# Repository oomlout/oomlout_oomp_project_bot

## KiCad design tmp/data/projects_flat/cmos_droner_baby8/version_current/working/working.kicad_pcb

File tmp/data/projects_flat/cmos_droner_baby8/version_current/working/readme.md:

# baby8 by cmos-droner  
This is a harvested standardized copy of a project from github.  
The original project can be found at:  
https://github.com/cmos-droner/baby8  
Please consult that link for additional, details, files, and license information.  
Note: It was auto harvested and if the original repo had more than one board file or anything out of the ordinary the files here are likely not representative.

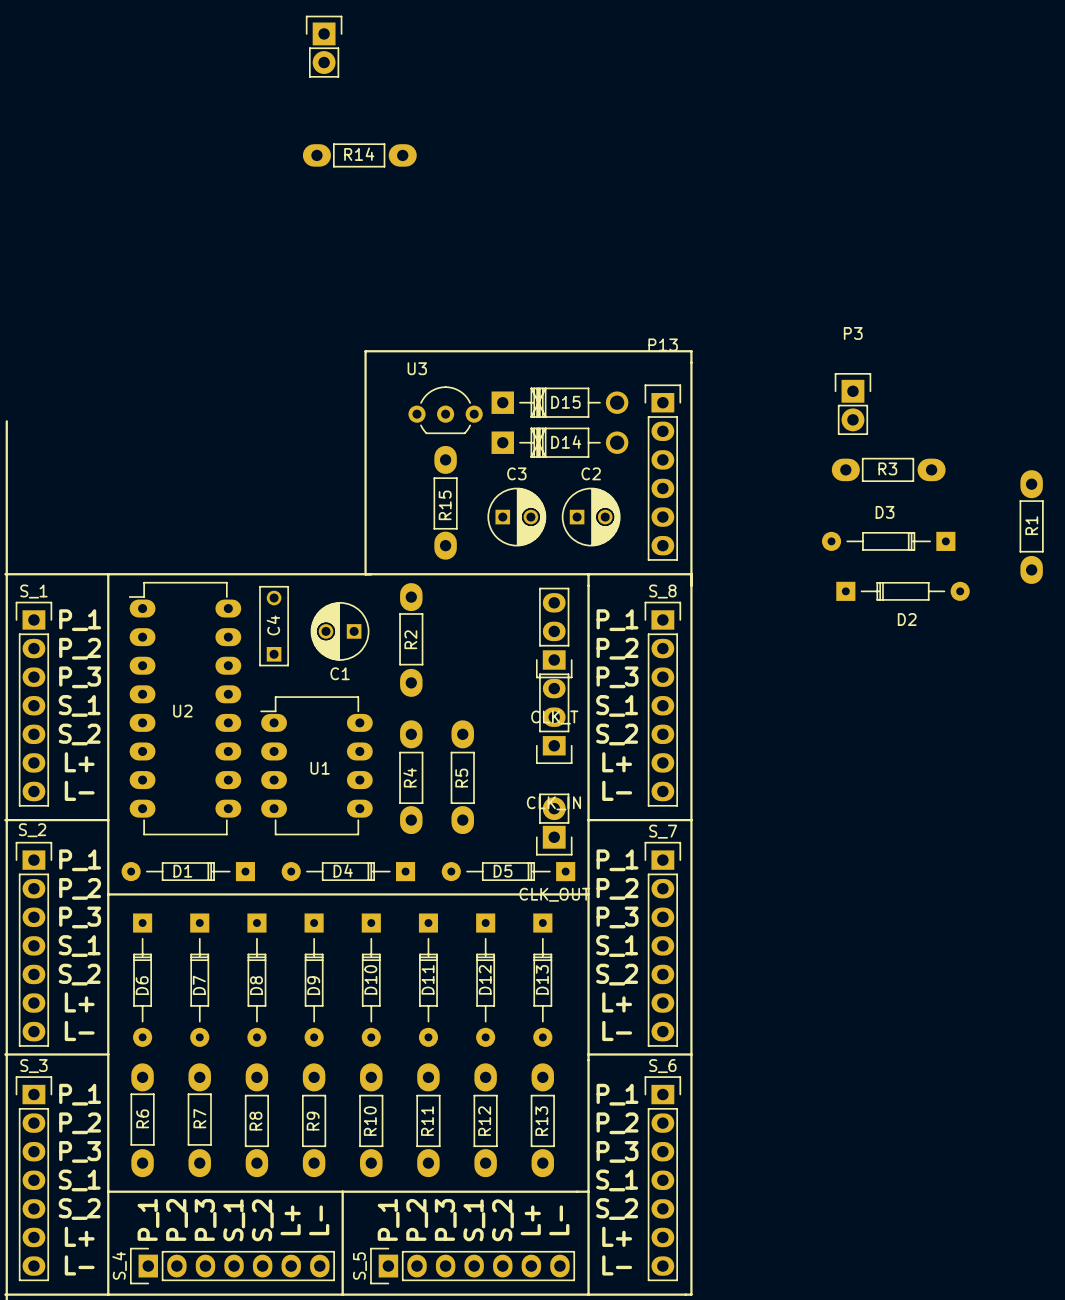
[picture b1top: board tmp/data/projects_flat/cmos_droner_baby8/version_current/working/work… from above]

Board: 2 copper layers, 51 parts (0 on the bottom side), 47 nets, no tracks yet.

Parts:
C1: 10uF; C_Radial_D5_L11_P2.5
C2: 220uF; C_Radial_D5_L11_P2.5
C3: 47uF; C_Radial_D5_L11_P2.5
C4: 100nF; C_Rect_L7_W2.5_P5
CLK_IN: CLK_IN; Pin_Header_Straight_1x03
CLK_OUT: CLK_OUT; Pin_Header_Straight_1x02
CLK_T: CLK_TIME; Pin_Header_Straight_1x03
D1, D2, D3, D4, D5, D6, D7, D8, D9, D10, D11, D12, D13: 1N4148; Diode_DO-35_SOD27_Horizontal_RM10
D14, D15: 1N4004; Diode_DO-41_SOD81_Horizontal_RM10
P3: RST; Pin_Header_Straight_1x02
P13: PWR; Pin_Header_Straight_1x06
P14: CV_OUT; Pin_Header_Straight_1x02
R1, R2, R5, R14: 1k; Resistor_Horizontal_RM7mm_Wide
R3, R4: 20k; Resistor_Horizontal_RM7mm_Wide
R6, R7, R8, R9, R10, R11, R12, R13, R15: 10k; Resistor_Horizontal_RM7mm_Wide
S_1: STEP_1; Pin_Header_Straight_1x07
S_2: STEP_2; Pin_Header_Straight_1x07
S_3: STEP_3; Pin_Header_Straight_1x07
S_4: STEP_4; Pin_Header_Straight_1x07
S_5: STEP_5; Pin_Header_Straight_1x07
S_6: STEP_6; Pin_Header_Straight_1x07
S_7: STEP_7; Pin_Header_Straight_1x07
S_8: STEP_8; Pin_Header_Straight_1x07
U1: LM555N; DIP-8_W7.62mm_LongPads
U2: 4017; DIP-16_W7.62mm_LongPads
U3: LM7805; TO-92_Inline_Wide

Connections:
+5V: C3.1, C4.1, CLK_T.1, D2.1, D4.1, D15.2, U1.4, U1.8, U2.16, U3.3
GND: C1.2, C2.2, C3.2, C4.2, CLK_IN.1, CLK_OUT.1, D3.2, D5.2, D14.2, P3.1, P13.1, P13.6, P14.1, R1.2, R5.1, S_1.3, S_1.7, S_2.3, S_2.7, S_3.3, S_3.7, S_4.3, S_4.7, S_5.3, S_5.7, S_6.3, S_6.7, S_7.3, S_7.7, S_8.3, S_8.7, U1.1, U2.8, U3.2
unnamed: C1.1, R2.2, U1.2, U1.6
unnamed: C2.1, D14.1, D15.1, P13.4, R15.2, U3.1
unnamed: CLK_OUT.2, D1.1
unnamed: D1.2, R4.2, U2.14
unnamed: D2.2, D3.1, P3.2, R1.1, R3.2
unnamed: CLK_IN.3, D4.2, D5.1, R4.1, R5.2
unnamed: D6.1, S_1.4
unnamed: D6.2, S_1.2
unnamed: D7.1, S_2.4
unnamed: D7.2, S_2.2
unnamed: D8.1, S_3.4
unnamed: D8.2, S_3.2
unnamed: D9.1, S_4.4
unnamed: D9.2, S_4.2
unnamed: D10.1, S_5.4
unnamed: D10.2, S_5.2
unnamed: D11.1, S_6.4
unnamed: D11.2, S_6.2
unnamed: D12.1, S_7.4
unnamed: D12.2, S_7.2
unnamed: D13.1, S_8.4
unnamed: D13.2, S_8.2
unnamed: CLK_IN.2, U1.3
unnamed: CLK_T.2, CLK_T.3, R2.1, U1.7
unnamed: R6.2, S_1.1, U2.3
unnamed: R6.1, S_1.6
unnamed: R7.2, S_2.1, U2.2
unnamed: R7.1, S_2.6
unnamed: R8.2, S_3.1, U2.4
unnamed: R8.1, S_3.6
unnamed: R9.2, S_4.1, U2.7
unnamed: R9.1, S_4.6
unnamed: R10.2, S_5.1, U2.10
unnamed: R10.1, S_5.6
unnamed: R11.2, S_6.1, U2.1
unnamed: R14.2, S_1.5, S_2.5, S_3.5, S_4.5, S_5.5, S_6.5, S_7.5, S_8.5
unnamed: R11.1, S_6.6
unnamed: R12.2, S_7.1, U2.5
unnamed: R12.1, S_7.6
unnamed: R13.2, S_8.1, U2.6
unnamed: R13.1, S_8.6
unnamed: P13.2, P13.3
unnamed: P13.5, R15.1
unnamed: P14.2, R14.1
unnamed: R3.1, U2.9, U2.15

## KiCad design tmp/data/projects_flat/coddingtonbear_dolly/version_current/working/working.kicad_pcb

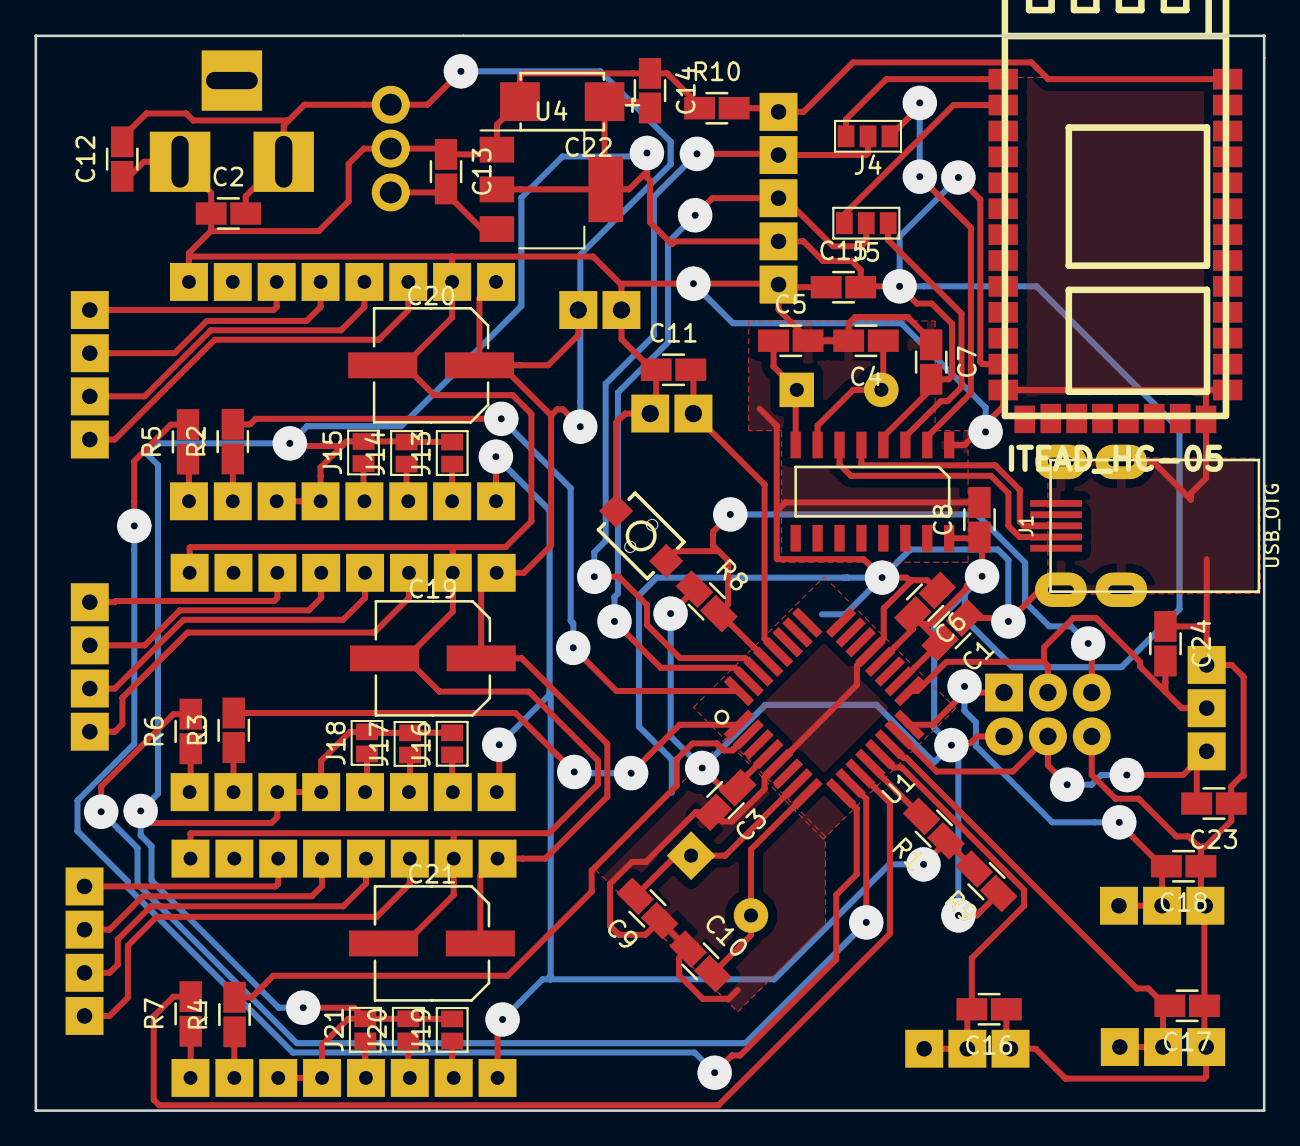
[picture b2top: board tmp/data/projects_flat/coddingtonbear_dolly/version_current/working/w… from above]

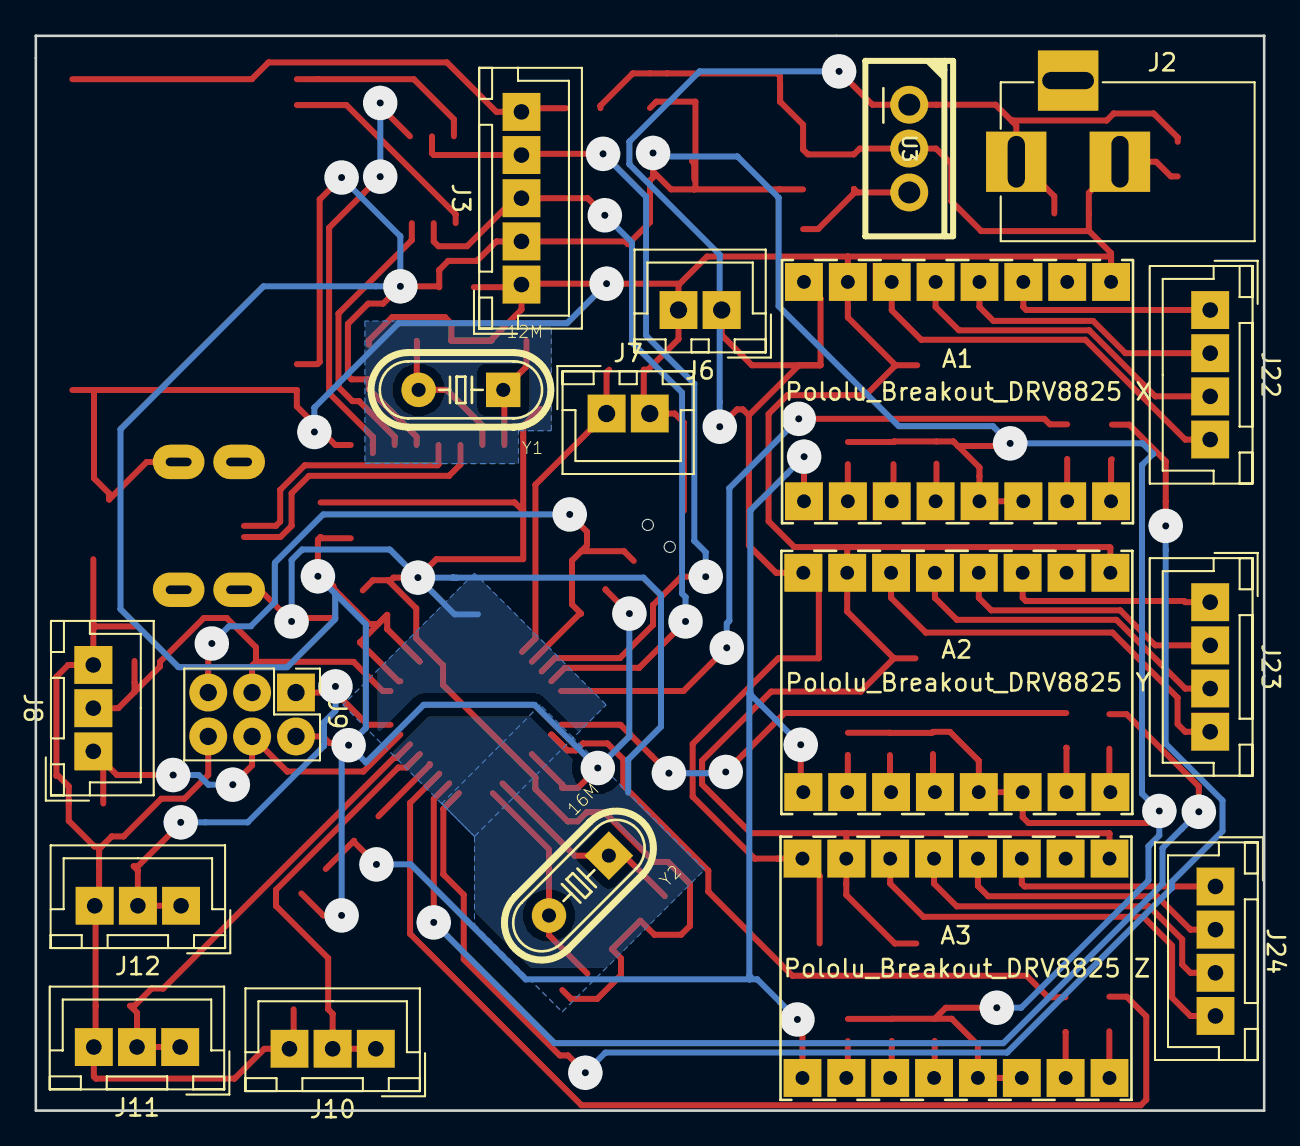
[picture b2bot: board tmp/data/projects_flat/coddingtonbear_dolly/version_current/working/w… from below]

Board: 2 copper layers, 71.1 x 62.2 mm, 69 parts (18 on the bottom side), 59 nets.

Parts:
A1: Pololu_Breakout_DRV8825 X; Pololu_Stepper_Breakout
A2: Pololu_Breakout_DRV8825 Y; Pololu_Stepper_Breakout
A3: Pololu_Breakout_DRV8825 Z; Pololu_Stepper_Breakout
C1, C2, C3, C6, C7, C8, C11, C14, C15, C16, C17, C18, C23, C24: 0.1u; 0805_Milling
C4, C5, C9, C10: 22p; 0805_Milling
C12, C13: 0.33u; 0805_Milling
C19, C20, C21: 100u; CAP-SMD-SIZE-D
C22: 220u; CAPACITOR_TANTALUM_C
J1: USB_OTG; UJ2-MIBH-4-SMT
J2: Barrel_Jack; BARREL_JACK
J3: UART; JST_XH_B05B-XH-A_05x2.50mm_Straight_LargePads
J4: RX; GS3
J5: TX; GS3
J6: 24V_Out; JST_XH_B02B-XH-A_02x2.50mm_Straight_LargePads
J7: Probe; JST_XH_B02B-XH-A_02x2.50mm_Straight_LargePads
J8: Spindle; JST_XH_B03B-XH-A_03x2.50mm_Straight_LargePads
J9: ICSP; Pin_Header_Straight_2x03_Pitch2.54mm
J10: X_End; JST_XH_B03B-XH-A_03x2.50mm_Straight_LargePads
J11: Y_End; JST_XH_B03B-XH-A_03x2.50mm_Straight_LargePads
J12: Z_End; JST_XH_B03B-XH-A_03x2.50mm_Straight_LargePads
J13, J14, J15, J16, J17, J18, J19, J20, J21: GS2
J22: X_Stepper; JST_XH_B04B-XH-A_04x2.50mm_Straight_LargePads
J23: Y_Stepper; JST_XH_B04B-XH-A_04x2.50mm_Straight_LargePads
J24: Z_Stepper; JST_XH_B04B-XH-A_04x2.50mm_Straight_LargePads
R1, R2, R3, R4, R5, R6, R7: 100; 0805_Milling
R8, R9, R10: 10k; 0805_Milling
SW1: SW_SPST; SW_PUSHBUTTON_TINY_2PIN
U1: ATMEGA328PB-AU; TQFP32_ATMEGA328P
U2: CH340G; SOIC-16
U3: L7805; TO-220
U4: AP1117-15; SOT-223-3Lead_TabPin2
U5: ITEAD_HC-05
Y1: 12M; XTAL_HC-49US-16.000MHZ
Y2: 16M; XTAL_HC-49US-16.000MHZ

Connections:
+3V3: A1.13, A1.14, A2.13, A2.14, A3.13, A3.14, C1.2, C3.1, C6.2, C7.2, C8.1, C14.2, C15.2, C22.1, J3.2, J9.2, J13.2, J14.2, J15.2, J16.2, J17.2, J18.2, J19.2, J20.2, J21.2, R8.1, R9.1, U1.4, U1.18, U1.20, U2.4, U2.16, U4.2, U5.12
+24V: A1.8, A2.8, A3.8, C2.2, C12.2, C19.1, C20.1, C21.1, J2.1, J6.1, U3.1
BT_IN: J5.1, U5.2
BT_KEY: J3.5, R10.2, U5.34
BT_OUT: J4.1, U5.1
GND: A1.1, A1.7, A2.1, A2.7, A3.1, A3.7, C1.1, C2.1, C3.2, C4.2, C5.2, C6.1, C7.1, C8.2, C9.1, C10.1, C11.1, C12.1, C13.1, C14.1, C15.1, C16.1, C17.1, C18.1, C19.2, C20.2, C21.2, C22.2, C23.1, C24.1, J1.5, J1.6, J2.2, J3.1, J6.2, J7.2, J8.3, J9.6, J10.3, J11.3, J12.3, R10.1, SW1.2, U1.5, U1.21, U2.1, U3.2, U4.1, U5.13, U5.21, U5.22
MISO: C18.2, J9.1, J12.1, J12.2, U1.16
MOSI: C23.2, J8.1, J9.4, U1.15
unnamed: A1.3, J22.1
unnamed: A1.4, J22.2
unnamed: A1.5, J22.3
unnamed: A1.6, J22.4
unnamed: A1.10, J13.1
unnamed: A1.11, J14.1
unnamed: A1.12, J15.1
unnamed: A2.3, J23.1
unnamed: A2.4, J23.2
unnamed: A2.5, J23.3
unnamed: A2.6, J23.4
unnamed: A2.10, J16.1
unnamed: A2.11, J17.1
unnamed: A2.12, J18.1
unnamed: A3.3, J24.1
unnamed: A3.4, J24.2
unnamed: A3.5, J24.3
unnamed: A3.6, J24.4
unnamed: A3.10, J19.1
unnamed: A3.11, J20.1
unnamed: A3.12, J21.1
unnamed: C4.1, U2.7, Y1.2
unnamed: C5.1, U2.8, Y1.1
unnamed: C9.2, U1.7, Y2.1
unnamed: C10.2, U1.8, Y2.2
unnamed: C13.2, U3.3, U4.3
unnamed: J1.2, U2.6
unnamed: J1.3, U2.5
unnamed: R1.2, U1.12
unnamed: R2.2, U1.32
unnamed: R3.2, U1.1
unnamed: R4.2, U1.2
unnamed: R5.2, U1.9
unnamed: R6.2, U1.10
unnamed: R7.2, U1.11
PROBE: C11.2, J7.1, U1.28
RST: J9.5, R8.2, SW1.1, U1.29
RX: J3.4, J4.2, U1.30
SCK: C24.2, J8.2, J9.3, U1.17
TX: J3.3, J5.2, U1.31
USB_IN: J5.3, U2.3
USB_OUT: J4.3, U2.2
XDIR: A1.16, R5.1
XEND: C16.2, J10.1, J10.2, U1.13
XSTEP: A1.15, R2.1
YDIR: A2.16, R6.1
YEND: C17.2, J11.1, J11.2, U1.14
YSTEP: A2.15, R3.1
ZDIR: A3.16, R7.1
ZSTEP: A3.15, R4.1
~ENABLE_STEPPER: A1.9, A2.9, A3.9, R1.1, R9.2

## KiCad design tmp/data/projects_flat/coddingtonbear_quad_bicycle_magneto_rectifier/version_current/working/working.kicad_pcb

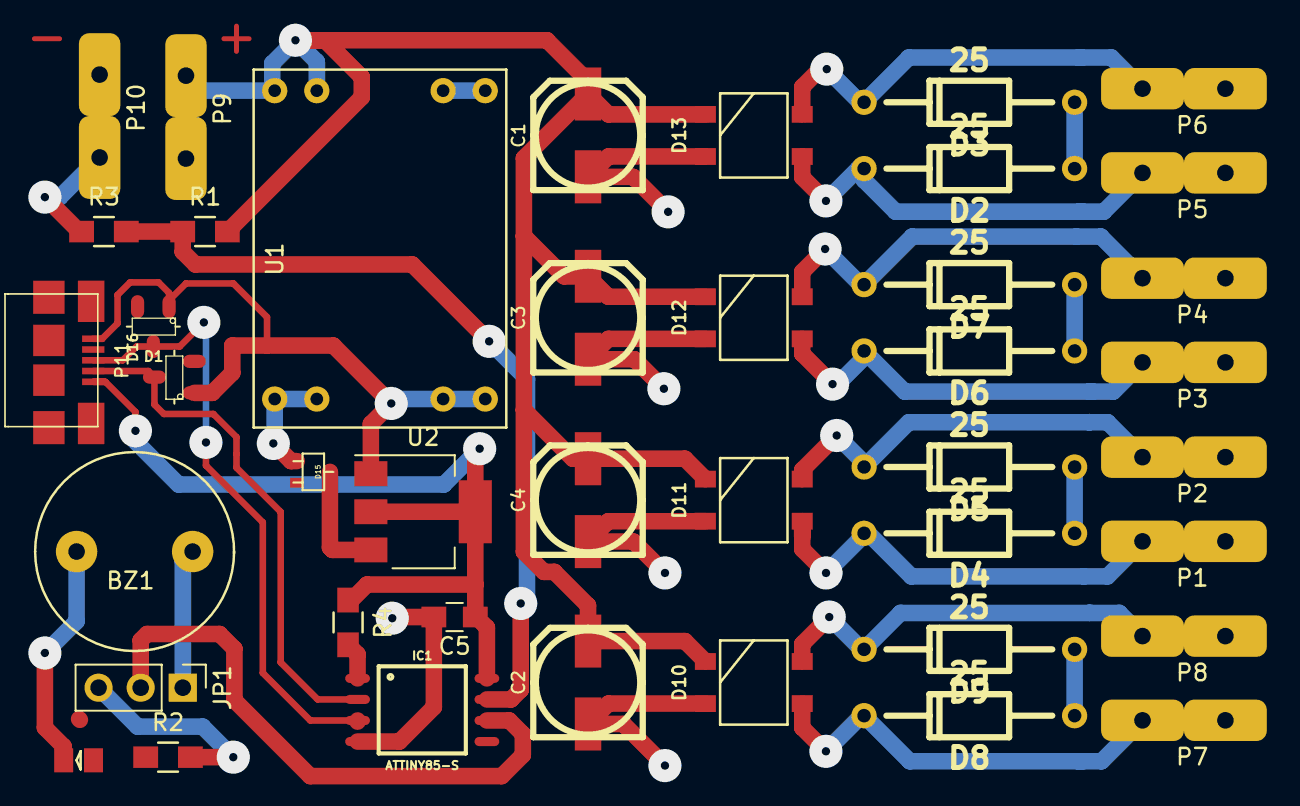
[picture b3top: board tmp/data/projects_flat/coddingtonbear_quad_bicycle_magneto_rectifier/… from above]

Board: 2 copper layers, 41 parts (0 on the bottom side), 25 nets.

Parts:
BZ1: Buzzer; 12mm_buzzer
C1, C2, C3, C4: ?; SMD_PANASONIC_D
C5: 0.1u; C_0805_HandSoldering
D1, D16: 3.6; DIODE-SOT-23-3
D2, D3, D4, D5, D6, D7, D8, D9: 25; DO204AL_500
D10, D11, D12, D13: MB24S(+); SM-TO-269AA
D14: LED; 0805-LED
D15: D; SOT323_diode
IC1: ATTINY85-S; SOIC8
JP1: Jumper_NC_Dual; Pin_Header_Straight_1x03_Pitch2.54mm
P1, P2, P3, P4, P5, P6, P7, P8: CONN_01X01; TAB
P9: VCC; TAB
P10: GND; TAB
P11: USB_OTG; MICRO-B_USB-INVERTED
R1: 1k; R_0805_HandSoldering
R2: 500; R_0805_HandSoldering
R3: 200; R_0805_HandSoldering
R4: 10k; R_0805_HandSoldering
U1: MP1584EN
U2: AP111750; SOT-223

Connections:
GND: BZ1.2, C1.2, C2.2, C3.2, C4.2, C5.2, D1.2, D10.2, D11.2, D12.2, D13.2, D14.1, D16.2, IC1.4, P10.1, P11.5, R3.1, U1.1, U1.3, U2.1
unnamed: BZ1.1, JP1.1
unnamed: D2.2, D3.2
unnamed: D4.2, D5.2
unnamed: D6.2, D7.2
unnamed: D8.2, D9.2
unnamed: D8.1, D10.3, P7.1
unnamed: D9.1, D10.4, P8.1
unnamed: D4.1, D11.3, P1.1
unnamed: D5.1, D11.4, P2.1
unnamed: D6.1, D12.3, P3.1
unnamed: D7.1, D12.4, P4.1
unnamed: D2.1, D13.3, P5.1
unnamed: D3.1, D13.4, P6.1
unnamed: D14.2, R2.1
unnamed: D15.1, U2.3
unnamed: D15.2, U1.4
unnamed: IC1.1, R4.2
unnamed: IC1.6, JP1.2
unnamed: IC1.7, R1.1, R3.2
unnamed: JP1.3, R2.2
USBD+: D16.1, IC1.3, P11.3
USBD-: D1.1, IC1.2, P11.2
VCC: C1.1, C2.1, C3.1, C4.1, D10.1, D11.1, D12.1, D13.1, P9.1, R1.2, U1.2
VUSB: C5.1, IC1.8, P11.1, R4.1, U2.2, U2.4

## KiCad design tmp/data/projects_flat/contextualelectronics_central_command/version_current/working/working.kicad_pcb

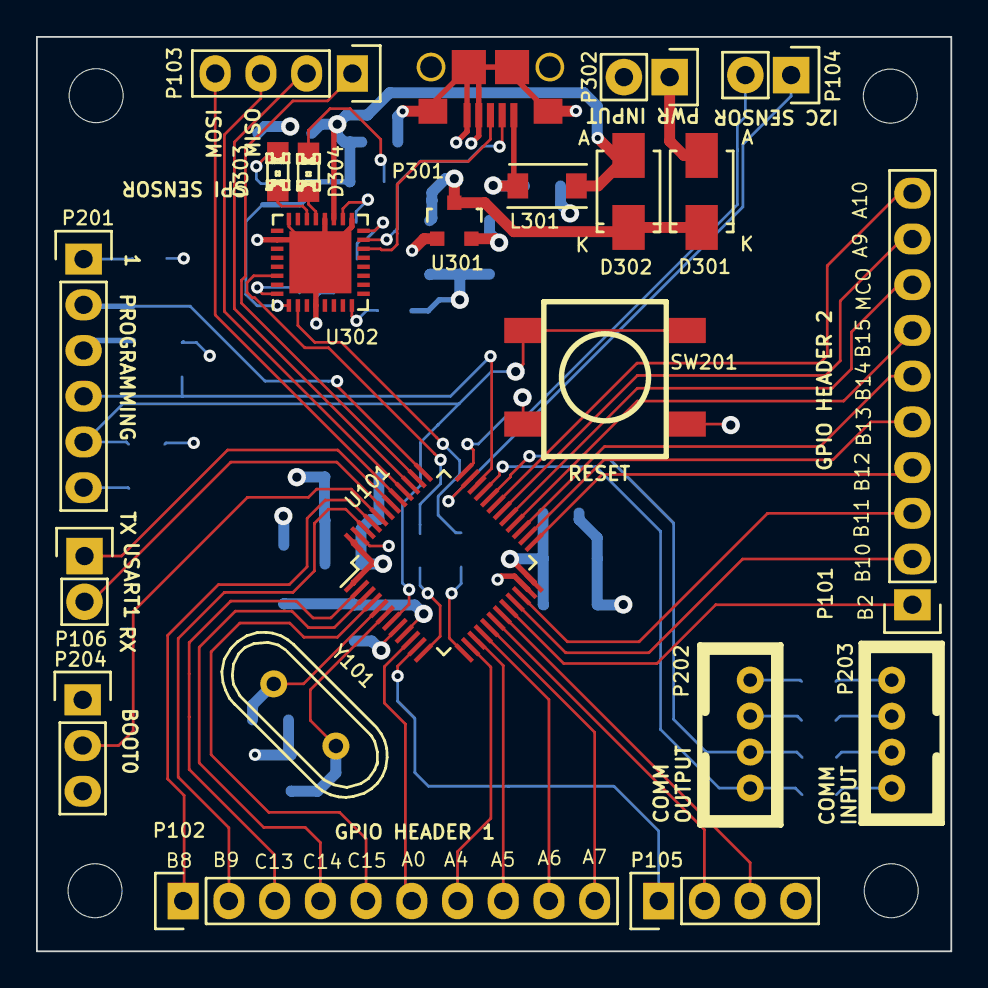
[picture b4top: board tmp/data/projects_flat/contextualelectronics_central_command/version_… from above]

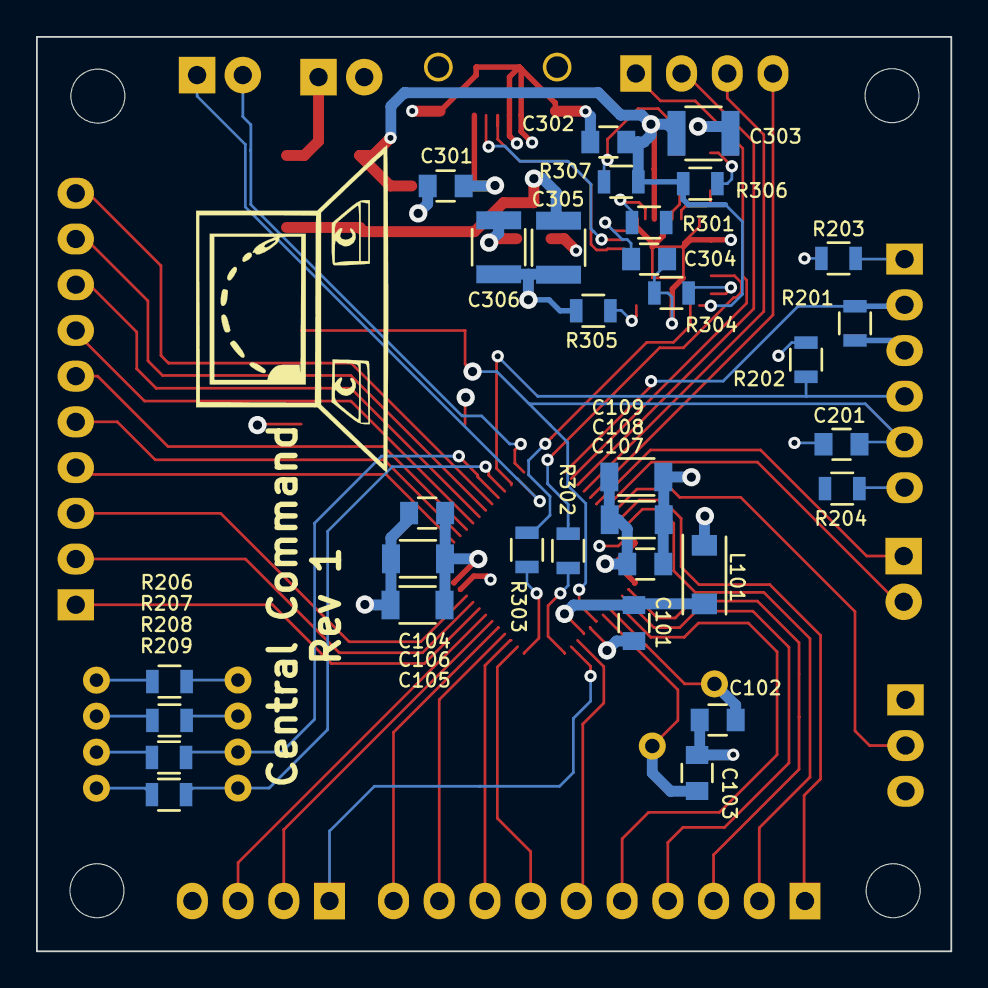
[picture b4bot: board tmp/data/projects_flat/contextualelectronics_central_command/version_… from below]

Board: 4 copper layers, 50.8 x 50.8 mm, 54 parts (32 on the bottom side), 66 nets.

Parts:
C101, C201: C; C_0805
C102, C103: 20P; C_0805
C104, C107, C301, C302, C304: .1U; C_0805
C105, C108: 1U; C_1206
C106, C109: 10U; C_1206
C303: 4.7U; C_1210
C305, C306: 10U; C_1210
D301, D302: D_Schottky; Diode-SMA_Standard
D303, D304: LED; LED-0805
L101: INDUCTOR; Neosid_Inductor_SM1206
L301: FERRITE; Neosid_Inductor_SM1206
P101, P102: CONN_01X10; Pin_Header_Straight_1x10
P103, P105: CONN_01X04; Pin_Header_Straight_1x04
P104, P106, P302: CONN_01X02; Pin_Header_Straight_1x02
P201: CONN_01X06; Pin_Header_Straight_1x06
P202, P203: CONN_01X04; Grove-2mm
P204: CONN_01X03; Pin_Header_Straight_1x03
P301: USB_B; 10118193
R201, R202, R204: R; R_0805
R203, R206, R207, R208, R209, R301, R302, R303: 0; R_0805
R304, R305: NOPE; R_0805
R306, R307: 270; R_0805
SW201: FSM2JSMAA-ND
U101: STM32F030C8; LQFP-48_7x7mm_Pitch0.5mm
U301: MCP1700T-3302E/TT_; SOT-23
U302: FT232RQ; QFN-32-1EP_5x5mm_Pitch0.5mm
Y101: Crystal; Crystal_HC49-U_Vertical

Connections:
/ADC_IN1: P105.1, U101.11
/ADC_IN8: P105.2, U101.18
/ADC_IN9: P105.3, U101.19
/Comm/BOOT0: P204.2, U101.44
/Comm/NRST: C201.1, P201.5, SW201.1, U101.7
/Comm/PWR: C104.1, C105.1, C106.1, C107.1, C108.1, C109.1, C306.1, L101.1, P202.2, P204.1, R202.1, R203.1, R207.1, U101.1, U101.24, U101.48, U301.2
/Comm/SCL: P202.3, R208.1, U101.32
/Comm/SDA: P202.4, R209.1, U101.33
/Comm/SWCLK: P201.2, R201.1, U101.37
/Comm/SWIO: P201.4, R202.2, U101.34
/I2C1_SCL: P104.2, U101.36
/I2C1_SDA: P104.1, U101.35
/MCO: P101.8, U101.29
/PA0: P102.6, U101.10
/PA4: P102.7, U101.14
/PA5: P102.8, U101.15
/PA6: P102.9, U101.16
/PA7: P102.10, U101.17
/PA9: P101.9, U101.30
/PA10: P101.10, U101.31
/PB2: P101.1, U101.20
/PB8: P102.1, U101.45
/PB9: P102.2, U101.46
/PB10: P101.2, U101.21
/PB11: P101.3, U101.22
/PB12: P101.4, U101.25
/PB13: P101.5, U101.26
/PB14: P101.6, U101.27
/PB15: P101.7, U101.28
/PC13: P102.3, U101.2
/PC14: P102.4, U101.3
/PC15: P102.5, U101.4
/Power/RXD: R303.1, U101.13
/Power/TXD: R302.1, U101.12
/Power/VCCIO: C302.1, C303.1, D302.2, L301.2, R306.1, R307.1, U302.1, U302.19
/SPI1_MISO: P103.3, U101.40
/SPI1_MOSI: P103.4, U101.41
/SPI1_NSS: P103.1, U101.38
/SPI1_SCK: P103.2, U101.39
/USART1_RX: P106.2, U101.43
/USART1_TX: P106.1, U101.42
/VDDA: C101.1, L101.2, U101.9
GND: C101.2, C102.1, C103.1, C104.2, C105.2, C106.2, C107.2, C108.2, C109.2, C201.2, C301.2, C302.2, C303.2, C304.2, C305.2, C306.2, P105.4, P201.3, P202.1, P204.3, P301.4, P301.5, P301.6, P301.7, P301.8, P301.9, P302.2, R201.2, R206.1, R304.1, R305.1, SW201.2, U101.8, U101.23, U101.47, U301.1, U302.4, U302.17, U302.20, U302.24, U302.26, U302.33
unnamed: C102.2, U101.5, Y101.1
unnamed: C103.2, U101.6, Y101.2
unnamed: C301.1, L301.1, P301.1
unnamed: C304.1, U302.16
unnamed: C305.1, D301.1, D302.1, U301.3
unnamed: D301.2, P302.1
unnamed: D303.1, U302.22
unnamed: D303.2, R306.2
unnamed: D304.1, U302.21
unnamed: D304.2, R307.2
unnamed: P201.1, R203.2
unnamed: P201.6, R204.1
unnamed: P203.1, R209.2
unnamed: P203.2, R208.2
unnamed: P203.3, R207.2
unnamed: P203.4, R206.2
unnamed: P301.2, U302.15
unnamed: P301.3, U302.14
unnamed: R301.1, U302.18
unnamed: R302.2, U302.30
unnamed: R303.2, U302.2
unnamed: R304.2, U302.32
unnamed: R305.2, U302.8

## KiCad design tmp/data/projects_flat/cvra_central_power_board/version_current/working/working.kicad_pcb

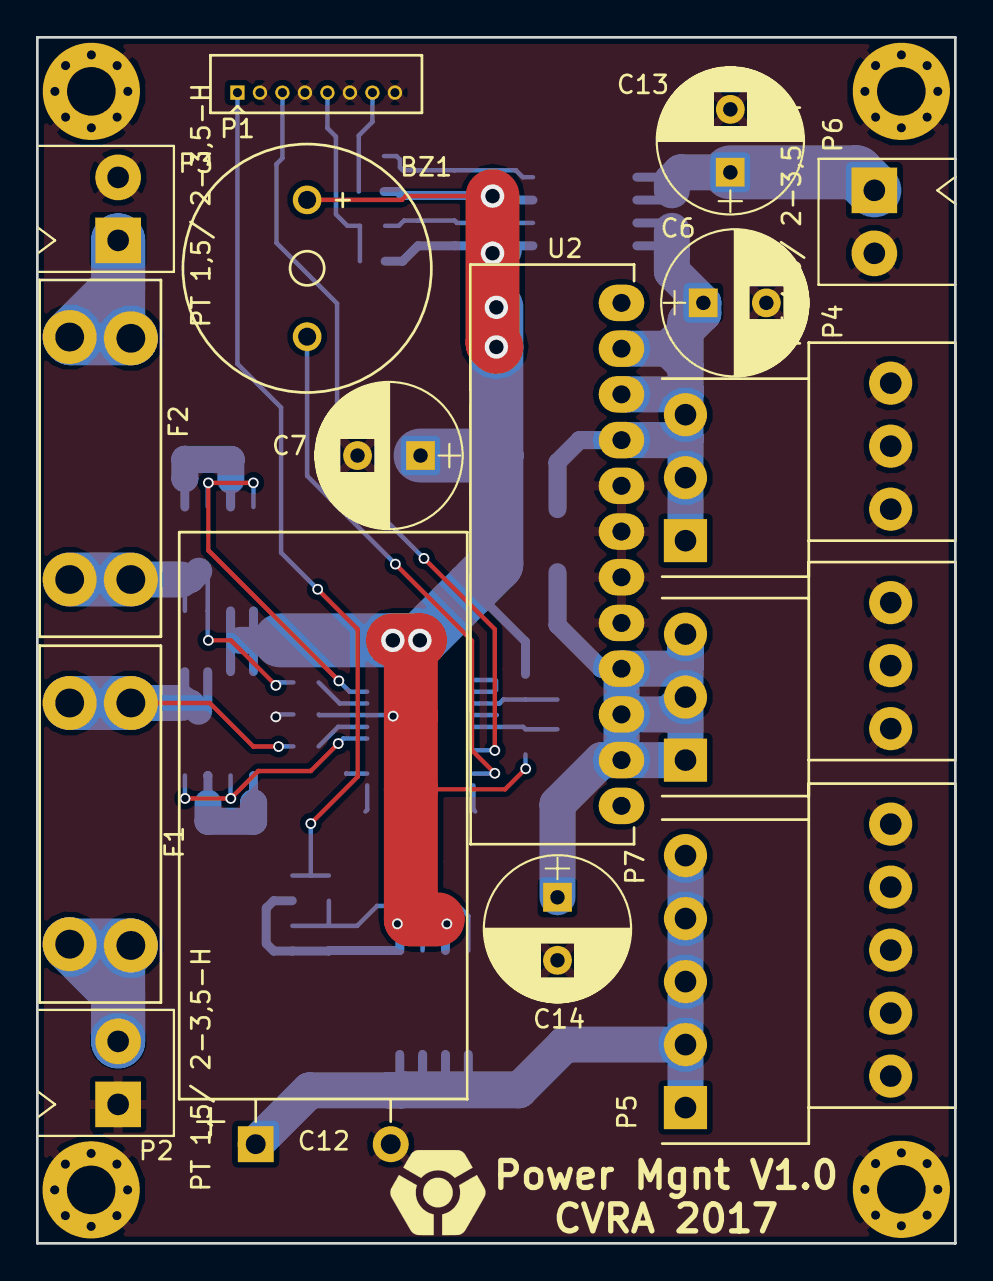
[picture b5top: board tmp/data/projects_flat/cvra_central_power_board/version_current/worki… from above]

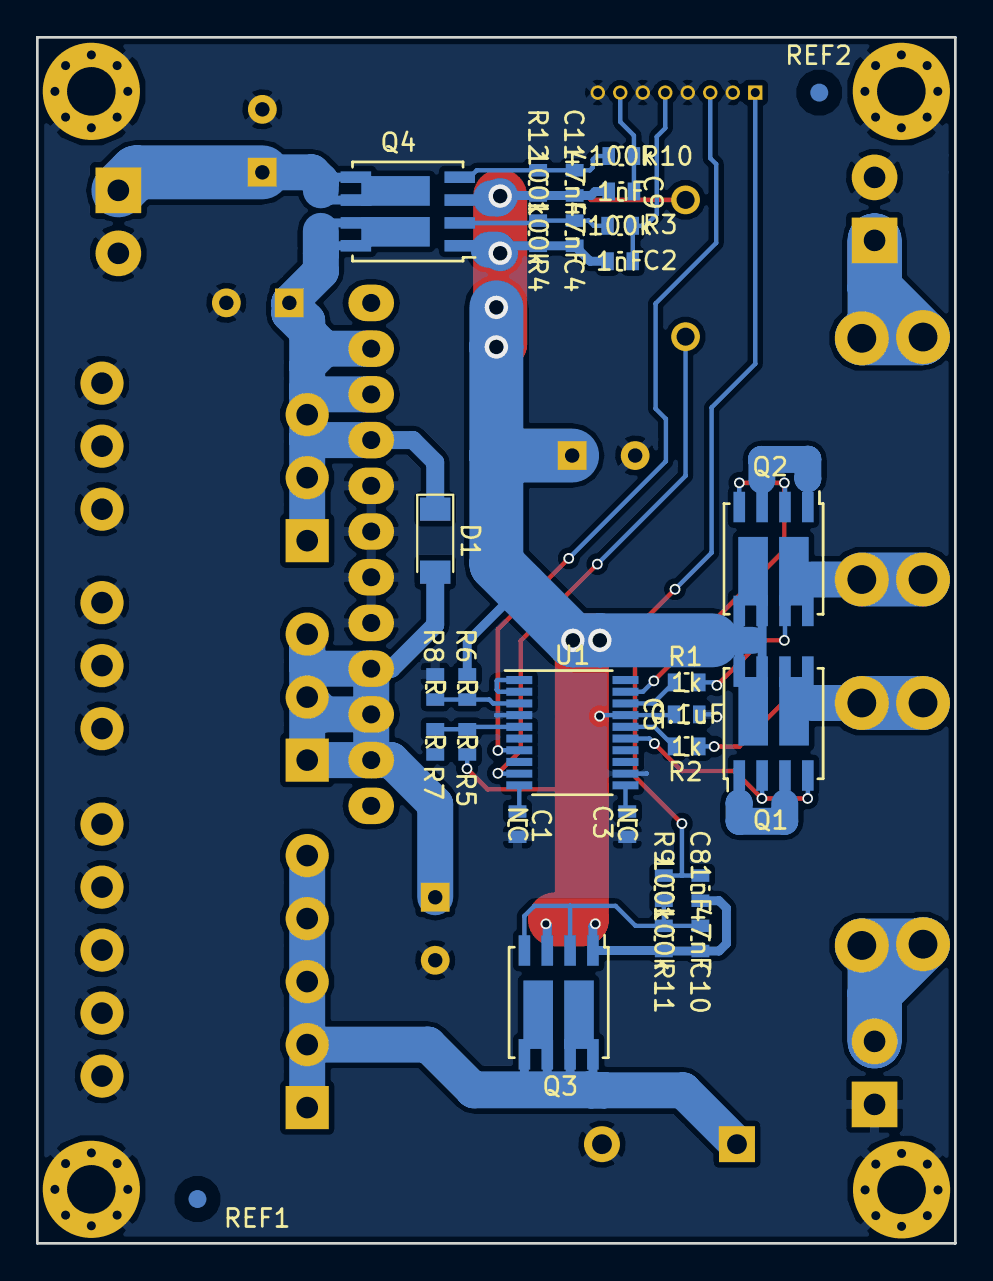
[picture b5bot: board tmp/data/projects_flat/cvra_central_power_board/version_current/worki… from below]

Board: 2 copper layers, 51.0 x 67.0 mm, 49 parts (27 on the bottom side), 29 nets.

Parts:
BZ1: Buzzer; _Buzzer_PUIAudio_AI-1433-TWT-R
C1, C3: NC; _0603
C2, C8, C9: 1nF; _0603
C4, C10, C11: 47nF; _0603
C5: 0.1uF; _0603
C6, C7, C13, C14: 100uF; CP_Radial_D8.0mm_P3.50mm
C12: 3.3mF; CP_Radial_L31.50D16.00P7.50_H
D1: LL103C-GS08; D_MiniMELF_Standard
F1, F2: 20A; FuseHolder-Keystone-3557-2
MEC1, MEC2, MEC3, MEC4: D2.7; MountingHole_2.7mm_M2.5_Pad_Via
P1: Picoblade; Molex-PicoBlade-8
P2, P3, P6: PT 1,5/ 2-3,5-H; Bornier_2p_3.5H
P4, P7: MKKDS 1/ 3-3,5; _Pheonix_MKKDS-1-3-3.5mm
P5: MKKDS 1/ 5-3,5; _Pheonix_MKKDS-1-5-3.5mm
Q1, Q2, Q3, Q4: Si7997DP; PowerPak-SO8_5.15x6.15mm_Pitch1.27mm
R1, R2: 1k; _0603
R3, R4, R9, R10, R11, R12: 100k; _0603
R5, R6, R7, R8: R; _0603
REF1, REF2: REF; Fiducial_1mm_Dia_2.54mm_Outer_CopperBottom
U1: LTC2952_TSSOP20; TSSOP-20_4.4x6.5mm_Pitch0.65mm
U2: R-555.0PA; DCDC-Conv_Recom_R-5xxxPA

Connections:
+5V: C14.1, D1.2, P7.1, P7.3, P7.5, U2.9, U2.10, U2.11
/~CMD_ON: C2.2, P1.5, R3.2
/~GLOBAL_ON: P1.3, U1.7
/~PC_ON: C9.2, P1.7, R10.2
/~PWR_ON: C8.2, P1.1, R9.2
GND: C1.2, C3.2, C5.2, C6.2, C7.2, C12.2, C13.2, C14.2, MEC1.1, MEC2.1, MEC3.1, MEC4.1, P1.2, P1.4, P1.6, P1.8, P2.1, P3.2, P4.2, P4.4, P4.6, P5.2, P5.4, P5.6, P5.8, P5.10, P6.2, P7.2, P7.4, P7.6, R7.1, R8.1, U1.4, U1.12, U2.5, U2.6, U2.7, U2.8
unnamed: BZ1.2, U1.9
unnamed: C1.1, U1.10
unnamed: C3.1, U1.11
unnamed: C4.2, Q4.2, R3.1, R4.2
unnamed: C10.2, Q3.2, Q3.4, R9.1, R11.2
unnamed: C11.2, Q4.4, R10.1, R12.2
unnamed: C12.1, P5.1, P5.3, P5.5, P5.7, P5.9, Q3.5, Q3.6, Q3.7, Q3.8
unnamed: C13.1, P6.1, Q4.5, Q4.6
unnamed: F1.1, Q1.5, Q1.6, R2.2
unnamed: F1.2, P2.2
unnamed: F2.1, Q2.7, Q2.8, R1.2
unnamed: F2.2, P3.1
unnamed: Q1.1, Q1.3
unnamed: Q1.2, Q1.4, U1.15
unnamed: Q2.1, Q2.3
unnamed: Q2.2, Q2.4, U1.19
unnamed: R1.1, U1.18
unnamed: R2.1, U1.16
unnamed: R5.2, R7.2, U1.5
unnamed: R6.2, R8.2, U1.3
unnamed: U1.1, U1.2
VCC: BZ1.1, C2.1, C4.1, C5.1, C7.1, C8.1, C9.1, C10.1, C11.1, Q1.7, Q1.8, Q2.5, Q2.6, Q3.1, Q3.3, Q4.1, Q4.3, R4.1, R5.1, R6.1, R11.1, R12.1, U1.17
VCOM: C6.1, D1.1, P4.1, P4.3, P4.5, Q4.7, Q4.8, U2.2, U2.3, U2.4

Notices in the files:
parts and their libraries:
Copyright 2016 Accelerated Designs. All rights reserved.
